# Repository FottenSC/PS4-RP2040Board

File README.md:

# Project 5001

Bill of materials:<br/>
1x <a href="https://www.digikey.com/en/products/detail/adafruit-industries-llc/5302/15794634">Adafruit KB2040 board</a><br/>
1x <a href="https://www.digikey.com/en/products/detail/w%C3%BCrth-elektronik/430451035836/5209030">6.2mm tactile switch</a><br/>
2x <a href="https://www.digikey.com/en/products/detail/c-k/THB001P/11687191">Joysticks</a><br/>

Forked from BeckyStern More info:
https://beckystern.com/?p=114849

### License
me do think you should read the license file full credit to BeckyStern

Sauces:
https://github.com/CountParadox/RP2040-Zero-Kicad

lol:
https://www.instructables.com/Salvage-USB-Gear-from-Discarded-Laptops/

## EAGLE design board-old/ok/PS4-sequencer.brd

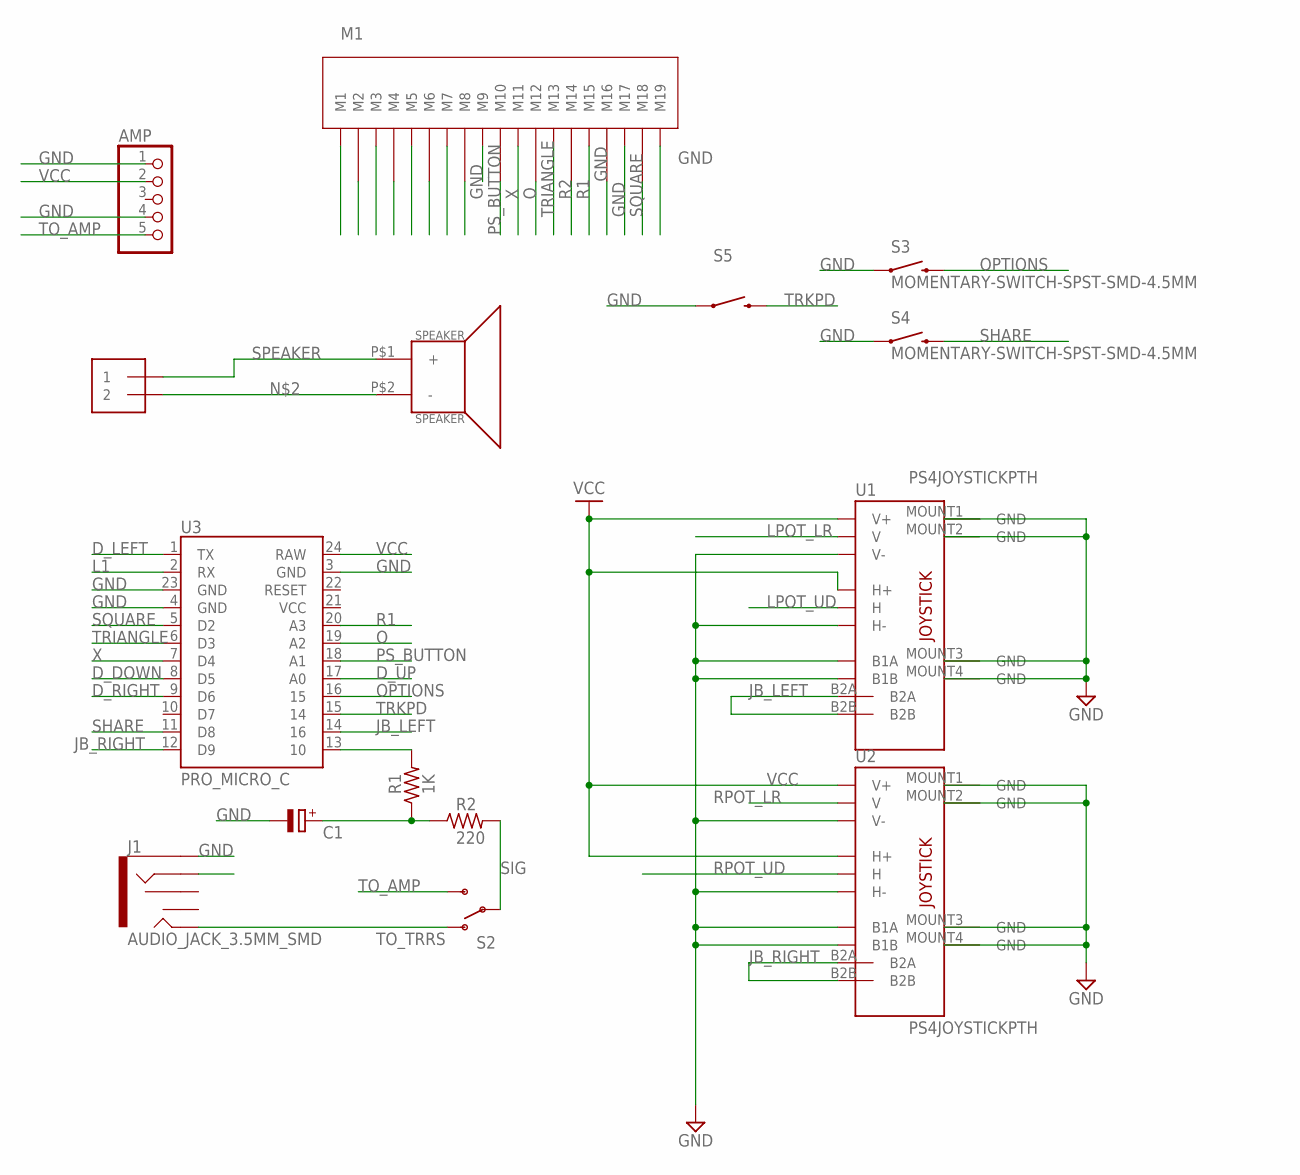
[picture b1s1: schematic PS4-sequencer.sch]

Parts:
AMP: PINHD-1X5; 1X05
C1: CAPACITOR-POLRADIAL-5MM-DIA; CAPPRD254W65D500H1150B
J1: AUDIO_JACK_3.5MM_SMD; AUDIO-JACK-3.5MM-SMD
J2: 1X2-3.5MM
M1: PS4MEMBRANE
R1: 1K; RESAD724W46L381D178B
R2: 220; RESAD724W46L381D178B
S2: SWITCH-SPDTSMD; SWITCH_SPDT_SMD
S3, S4: MOMENTARY-SWITCH-SPST-SMD-4.5MM; TACTILE_SWITCH_SMD_3.6MM
S5: TAC_SWITCHSMD; TACTILE_SWITCH_SMD_6MM
SPEAKER: SPEAKER; PS4_SPEAKER
U1, U2: PS4JOYSTICKPTH; PS4JOYSTICK
U3: PRO_MICRO_C

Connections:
D_DOWN: M1.8 (M8), U3.8 (D5)
D_LEFT: M1.7 (M7), U3.1 (TX)
D_RIGHT: M1.5 (M5), U3.9 (D6)
D_UP: M1.6 (M6), U3.17 (A0)
GND: AMP.1, AMP.4, C1.2 (-), J1.SLEEVE, M1.3 (M3), M1.9 (M9), M1.16 (M16), M1.17 (M17), M1.19 (M19), S3.2 (1), S3.3 (1), S4.2 (1), S4.3 (1), S5.1, U1.B1A, U1.B1B, U1.H3 (H-), U1.MOUNT1 (GND), U1.MOUNT2 (GND), U1.MOUNT3 (GND), U1.MOUNT4 (GND), U1.V3 (V-), U2.B1A, U2.B1B, U2.H3 (H-), U2.MOUNT1 (GND), U2.MOUNT2 (GND), U2.MOUNT3 (GND), U2.MOUNT4 (GND), U2.V3 (V-), U3.3 (GND), U3.4 (GND), U3.23 (GND)
JB_LEFT: U1.B2A, U1.B2B, U3.14 (16)
JB_RIGHT: U2.B2A, U2.B2B, U3.12 (D9)
L1: M1.2 (M2), U3.2 (RX)
L2: M1.1 (M1)
LPOT_LR: U1.V2 (V)
LPOT_UD: U1.H2 (H)
unnamed: C1.1 (+), R1.1, R2.1
unnamed: J2.2, SPEAKER.P$2 (-)
unnamed: R1.2, U3.13 (10)
O: M1.12 (M12), U3.19 (A2)
OPTIONS: S3.1 (2), S3.4 (2), U3.16 (15)
PS_BUTTON: M1.10 (M10), U3.18 (A1)
R1: M1.15 (M15), U3.20 (A3)
R2: M1.14 (M14)
RPOT_LR: U2.V2 (V)
RPOT_UD: U2.H2 (H)
SHARE: S4.1 (2), S4.4 (2), U3.11 (D8)
SIG: R2.2, S2.2
SPEAKER: J2.1, SPEAKER.P$1 (+)
SQUARE: M1.18 (M18), U3.5 (D2)
TO_AMP: AMP.5, S2.3 (S)
TO_TRRS: J1.TIP, S2.1 (O)
TRIANGLE: M1.13 (M13), U3.6 (D3)
TRKPD: S5.3 (2), U3.15 (14)
VCC: AMP.2, U1.H1 (H+), U1.V1 (V+), U2.H1 (H+), U2.V1 (V+), U3.24 (RAW)
X: M1.11 (M11), U3.7 (D4)

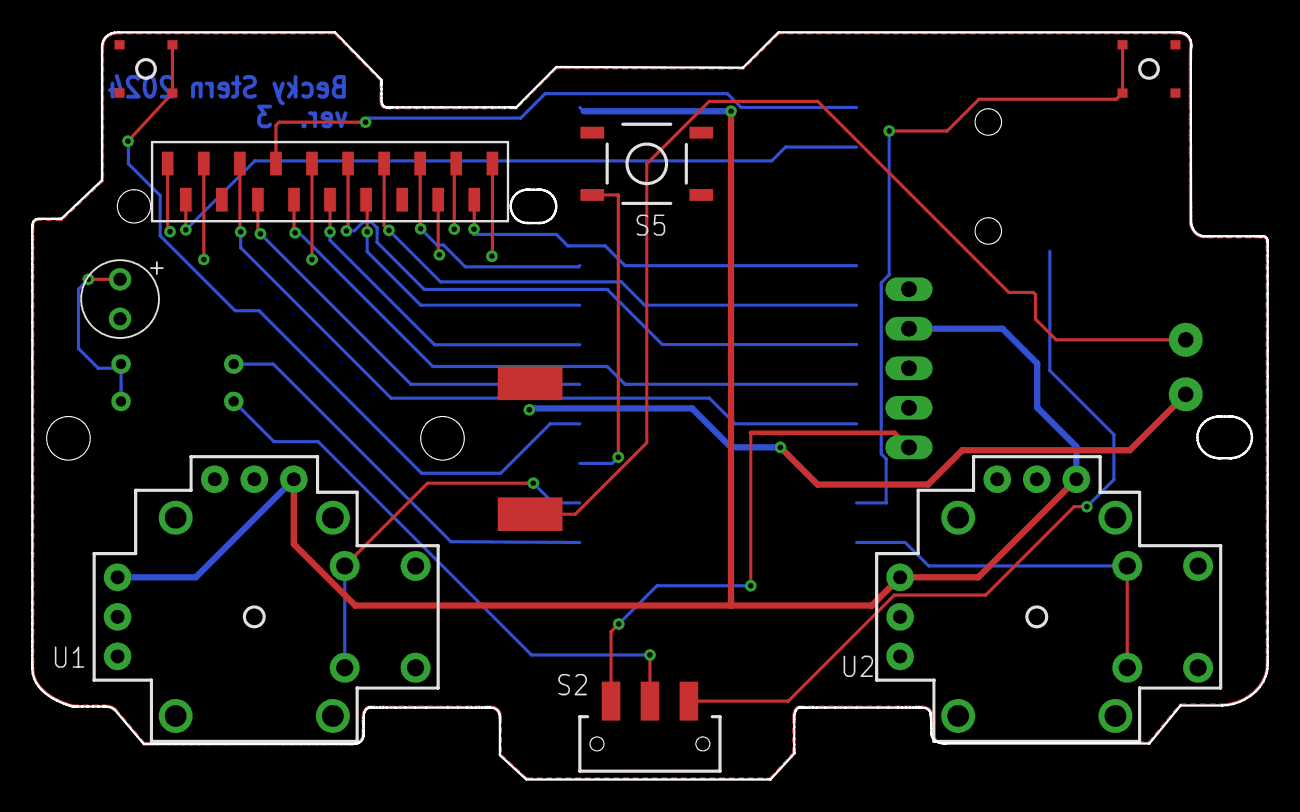
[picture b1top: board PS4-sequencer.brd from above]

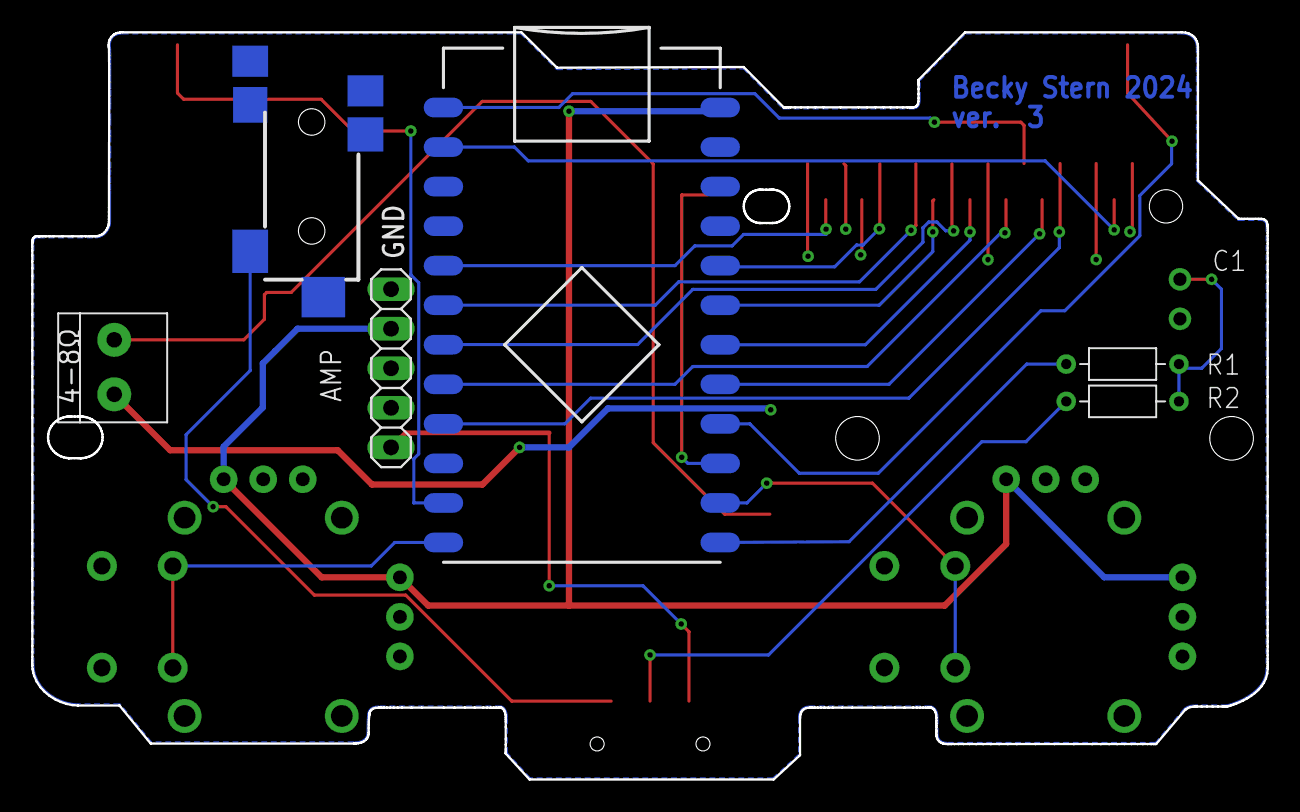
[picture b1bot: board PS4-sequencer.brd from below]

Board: 2 copper layers, 79.3 x 48.0 mm, 15 parts (6 on the bottom side), 25 nets.

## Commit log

2025-06-23 init

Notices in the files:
parts and their libraries:
SparkFun-Boards: Licensing: Creative Commons ShareAlike 4.0 International - https://creativecommons.org/licenses/by-sa/4.0
